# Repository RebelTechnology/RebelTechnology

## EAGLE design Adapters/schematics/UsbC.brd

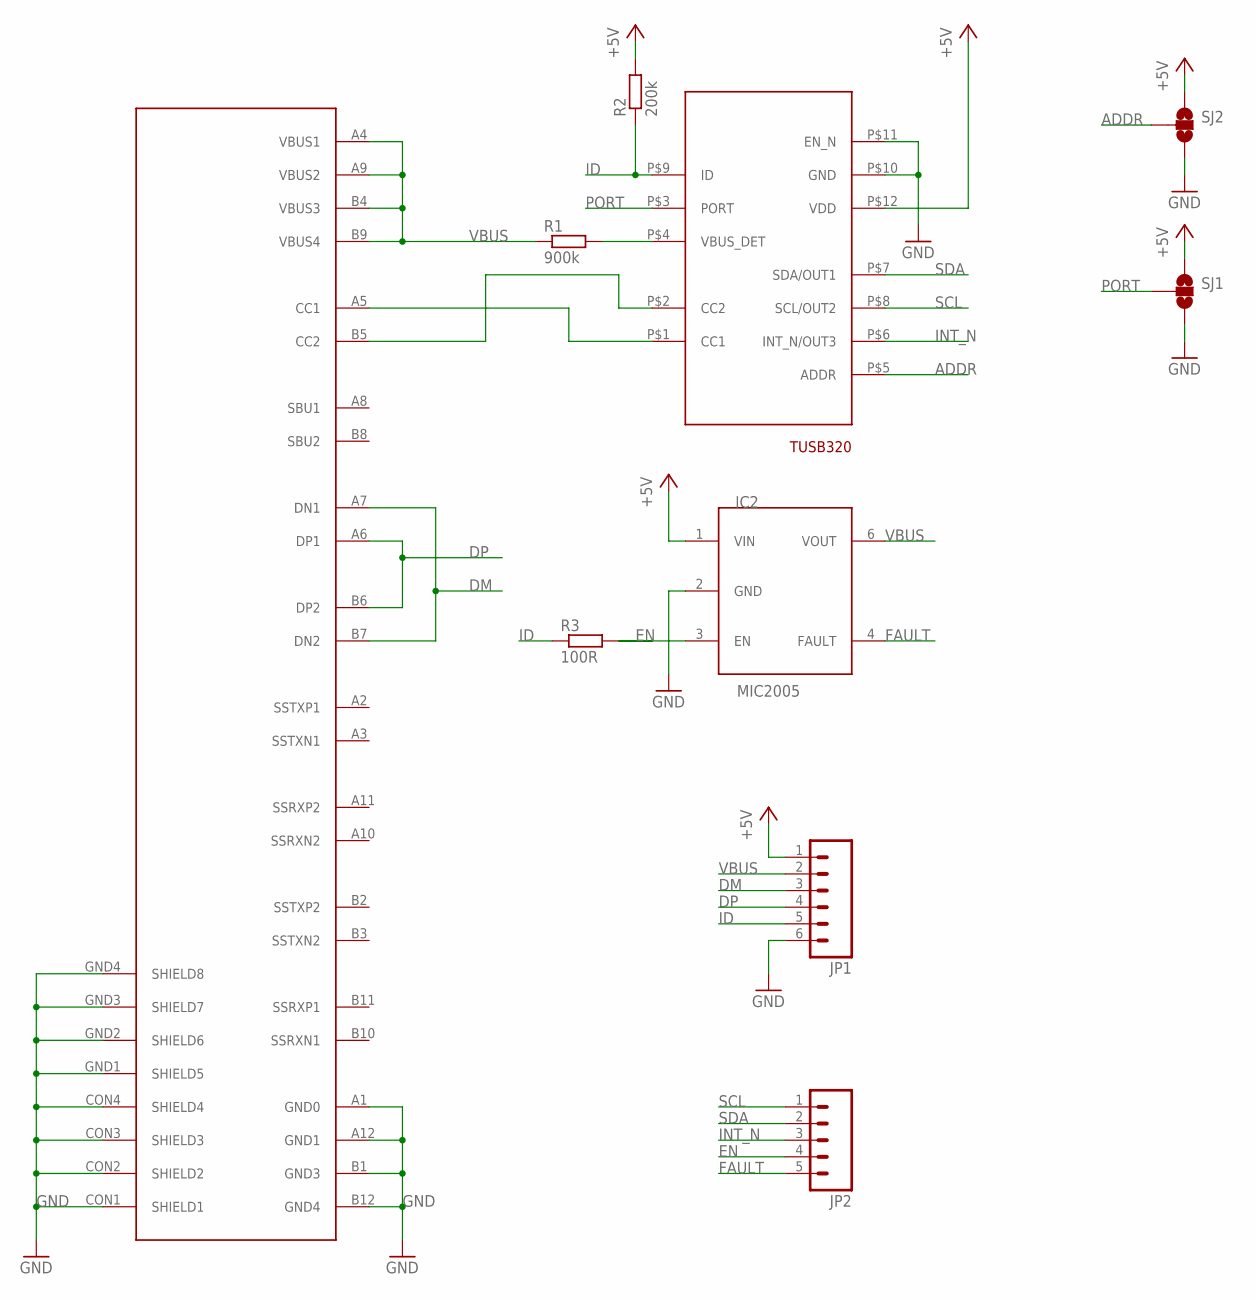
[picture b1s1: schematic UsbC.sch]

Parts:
CONN1: USB-C_WURTH_632723X00011USB-C; USB-C_WURTH_632723X00011
IC1: TUSB320XQFN; X2QFN
IC2: MIC2005; SOT23-6
JP1: M06SIP; 1X06
JP2: M05PTH; 1X05
R1: 900k; 0603
R2: 200k; 0603
R3: 100R; 0603
SJ1, SJ2: SOLDERJUMPER_2WAYS; SJ_3

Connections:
+5V: IC1.P$12 (VDD), IC2.1 (VIN), JP1.1, R2.2, SJ1.1, SJ2.1
ADDR: IC1.P$5 (ADDR), SJ2.2
CC1: CONN1.A5 (CC1), IC1.P$1 (CC1)
CC2: CONN1.B5 (CC2), IC1.P$2 (CC2)
DM: CONN1.A7 (DN1), CONN1.B7 (DN2), JP1.3
DP: CONN1.A6 (DP1), CONN1.B6 (DP2), JP1.4
EN: IC2.3 (EN), JP2.4, R3.2
FAULT: IC2.4 (FAULT), JP2.5
GND: CONN1.A1 (GND0), CONN1.A12 (GND1), CONN1.B1 (GND3), CONN1.B12 (GND4), CONN1.CON1 (SHIELD1), CONN1.CON2 (SHIELD2), CONN1.CON3 (SHIELD3), CONN1.CON4 (SHIELD4), CONN1.GND1 (SHIELD5), CONN1.GND2 (SHIELD6), CONN1.GND3 (SHIELD7), CONN1.GND4 (SHIELD8), IC1.P$10 (GND), IC1.P$11 (EN_N), IC2.2 (GND), JP1.6, SJ1.3, SJ2.3
ID: IC1.P$9 (ID), JP1.5, R2.1, R3.1
INT_N: IC1.P$6 (INT_N/OUT3), JP2.3
unnamed: IC1.P$4 (VBUS_DET), R1.2
PORT: IC1.P$3 (PORT), SJ1.2
SCL: IC1.P$8 (SCL/OUT2), JP2.1
SDA: IC1.P$7 (SDA/OUT1), JP2.2
VBUS: CONN1.A4 (VBUS1), CONN1.A9 (VBUS2), CONN1.B4 (VBUS3), CONN1.B9 (VBUS4), IC2.6 (VOUT), JP1.2, R1.1

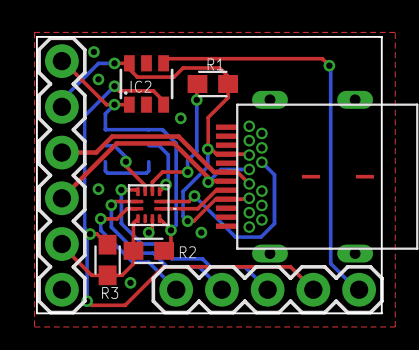
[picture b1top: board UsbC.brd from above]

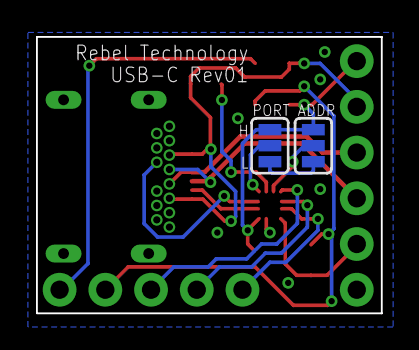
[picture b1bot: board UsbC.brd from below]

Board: 2 copper layers, 19.2 x 15.4 mm, 10 parts (2 on the bottom side), 16 nets.

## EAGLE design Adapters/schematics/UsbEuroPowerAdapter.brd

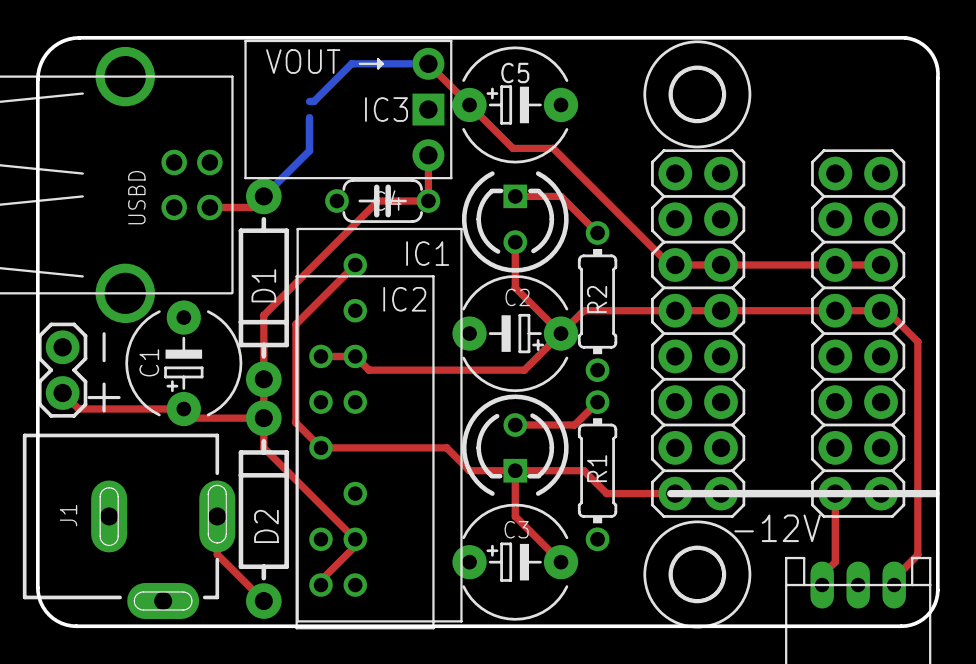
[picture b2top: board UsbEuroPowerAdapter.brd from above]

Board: 2 copper layers, 50.0 x 32.7 mm, 23 parts (1 on the bottom side), 9 nets.

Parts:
C1, C2, C3, C5: 47u; E5-6
C4: 100n; C050-024X044
D1: 1N5817; DIODE-1N4001
D2: 1N4001; DIODE-1N4001
EXT: CON-JST_PH_3W
IC1: TEC-2SIP; TEC-2
IC2: TBA-2SIP; TBA-2
IC3: REG_S9V11F5
J1: POWER_JACK; DC_JACK_SLOT
JP1: 1X02
LED1, LED2: LED3MM
R1, R2: 2k; 0204/7
U$1, U$3: 2,8
U$2, U$6: M08X2; 2X8
USBD: USB-B-H
VBUS_5V: SOLDERJUMPERNO; SJ_2S-NO

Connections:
+5V: C5.+, IC3.VOUT, U$2.11, U$2.12, U$6.11, U$6.12, VBUS_5V.2
+9V: C1.+, C4.1, D1.C, D2.C, IC1.P2, IC2.P1, IC3.VIN, JP1.2
+12V: C2.+, EXT.P3, IC1.P6, IC2.P6, LED2.A, U$2.9, U$2.10, U$6.9, U$6.10
-12V: C3.-, EXT.P1, IC1.P8, IC2.P4, LED1.K, U$2.1, U$2.2, U$6.1, U$6.2
EXT_USB_D_VBUS: D1.A, USBD.VBUS, VBUS_5V.1
GND: C1.-, C2.-, C3.+, C4.2, C5.-, EXT.P2, IC1.P1, IC1.P7, IC2.P2, IC2.P5, IC3.GND, J1.GND, J1.GNDBREAK, JP1.1, R1.1, R2.1, U$2.3, U$2.4, U$2.5, U$2.6, U$2.7, U$2.8, U$6.3, U$6.4, U$6.5, U$6.6, U$6.7, U$6.8, USBD.GND
unnamed: LED2.K, R2.2
unnamed: LED1.A, R1.2
unnamed: D2.A, J1.PWR

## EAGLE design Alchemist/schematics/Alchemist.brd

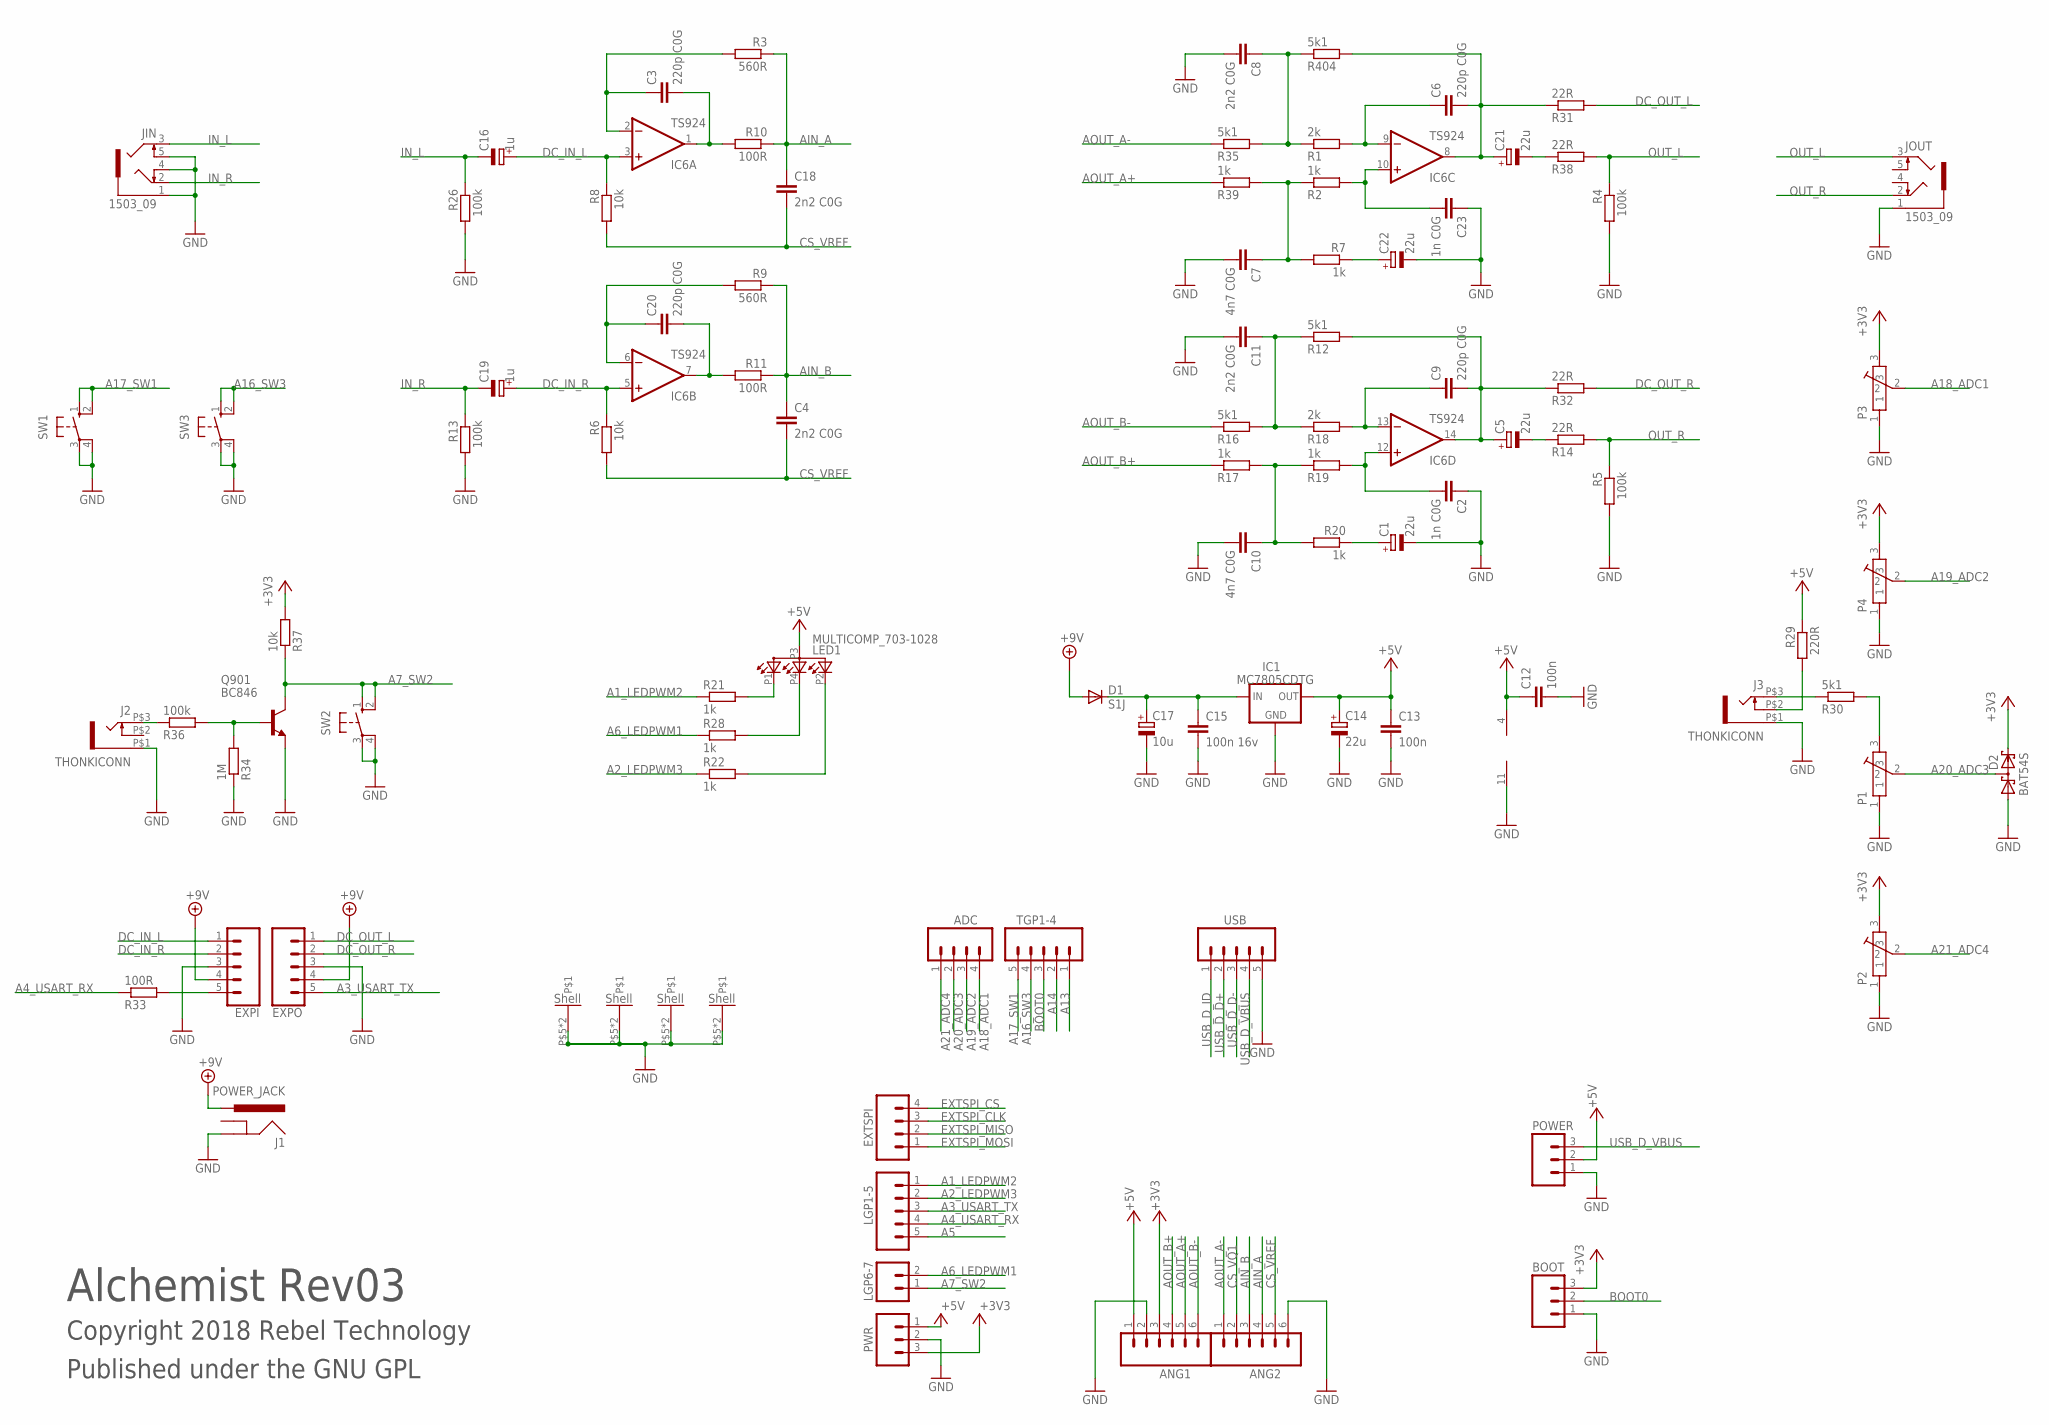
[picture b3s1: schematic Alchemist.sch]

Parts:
ADC: M04PTH; 1X04
ANG1, ANG2: M06SIP; 1X06
BOOT: M03PTH; 1X03
C1, C5, C14, C21, C22: 22u; CPOL-5
C2, C23: 1n C0G; C0603
C3, C6, C9, C20: 220p C0G; C0603
C4, C8, C11, C18: 2n2 C0G; C0603
C7, C10: 4n7 C0G; C0603
C12, C13: 100n; C0603
C15: 100n 16v; C0603
C16, C19: 1u; 153CLV-0405
C17: 10u; 153CLV-0405
D1: S1J; SMA-DIODE
D2: BAT54S; SOT23
EXPI: CONN_05JST-VERT; JST-5-PTH-VERT
EXPO: CONN_05JST-VERT; JST-5-PTH-VERT
EXTSPI: M04PTH; 1X04
IC1: MC7805CDTG; DPACK
IC6: TS924; SO14
J1: POWER_JACK; DC_JACK_SLOT
J2, J3: THONKICONN
JIN: 1503_09
JOUT: 1503_09
LED1: MULTICOMP_703-1028; RGB-LED-703-1028
LGP1-5: M05PTH; 1X05
LGP6-7: M02PTH; 1X02
P1, P2, P3, P4: POT-ALPS-RK09L1140
POWER: M03PTH; 1X03
PWR: M03PTH; 1X03
Q901: BC846; SOT23
R1, R18: 2k; 0603
R2, R7, R17, R19, R20, R21, R22, R28, R39: 1k; 0603
R3, R9: 560R; 0603
R4, R5, R13, R26, R36: 100k; 0603
R6, R8, R37: 10k; 0603
R10, R11, R33: 100R; 0603
R12, R16, R30, R35, R404: 5k1; 0603
R14, R31, R32, R38: 22R; 0603
R29: 220R; 0603
R34: 1M; 0603
SW1, SW2, SW3: 10-XX; B3F-10XX
TGP1-4: M05PTH; 1X05
USB: M05PTH; 1X05

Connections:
+3V3: ANG1.3, BOOT.3, D2.2 (C2), P2.3, P3.3, P4.3, PWR.3, R37.2
+5V: ANG1.1, C12.1, C13.1, C14.+, IC1.3 (OUT), IC6.4 (V+), LED1.P3 (A), POWER.2, PWR.1, R29.1
+9V: D1.A, EXPI.4, EXPO.4, J1.PWR
A1_LEDPWM2: LGP1-5.1, R21.1
A2_LEDPWM3: LGP1-5.2, R22.1
A3_USART_TX: EXPO.5, LGP1-5.3
A4_USART_RX: LGP1-5.4, R33.1
A5: LGP1-5.5
A6_LEDPWM1: LGP6-7.2, R28.1
A7_SW2: LGP6-7.1, Q901.3 (C), R37.1, SW2.1 (S), SW2.2 (S1)
A13: TGP1-4.1
A14: TGP1-4.2
A16_SW3: SW3.1 (S), SW3.2 (S1), TGP1-4.4
A17_SW1: SW1.1 (S), SW1.2 (S1), TGP1-4.5
A18_ADC1: ADC.4, P3.2
A19_ADC2: ADC.3, P4.2
A20_ADC3: ADC.2, D2.3 (C1A2), P1.2
A21_ADC4: ADC.1, P2.2
AIN_A: ANG2.4, C18.1, R3.1, R10.1
AIN_B: ANG2.3, C4.1, R9.1, R11.1
AOUT_A+: ANG1.5, R39.1
AOUT_A-: ANG2.1, R35.1
AOUT_B+: ANG1.4, R17.1
AOUT_B-: ANG1.6, R16.1
BOOT0: BOOT.2, TGP1-4.3
CS_VQ1: ANG2.2
CS_VREF: ANG2.5, C4.2, C18.2, R6.2, R8.2
DC_IN_L: C16.+, EXPI.1, IC6.3 (+IN), R8.1
DC_IN_R: C19.+, EXPI.2, IC6.5 (+IN), R6.1
DC_OUT_L: EXPO.1, R31.2
DC_OUT_R: EXPO.2, R32.2
EXTSPI_CLK: EXTSPI.3
EXTSPI_CS: EXTSPI.4
EXTSPI_MISO: EXTSPI.2
EXTSPI_MOSI: EXTSPI.1
GND: ANG1.2, ANG2.6, BOOT.1, C1.-, C2.1, C7.2, C8.2, C10.2, C11.2, C12.2, C13.2, C14.-, C15.2, C17.-, C22.-, C23.1, D2.1 (A1), EXPI.3, EXPO.3, IC1.4 (GND), IC6.11 (V-), J1.GND, J2.P$1 (5), J3.P$1 (5), JIN.1, JIN.4, JIN.5, JOUT.1, P1.1, P1.P$5, P1.P$6, P2.1, P2.P$5, P2.P$6, P3.1, P3.P$5, P3.P$6, P4.1, P4.P$5, P4.P$6, POWER.1, PWR.2, Q901.2 (E), R4.2, R5.2, R13.2, R26.2, R34.1, SW1.3, SW1.4 (P1), SW2.3, SW2.4 (P1), SW3.3, SW3.4 (P1), USB.5
IN_L: C16.-, JIN.3, R26.1
IN_R: C19.-, JIN.2, R13.1
unnamed: EXPI.5, R33.2
unnamed: C3.1, IC6.2 (-IN), R3.2
unnamed: C20.2, IC6.7 (OUT), R11.2
unnamed: C20.1, IC6.6 (-IN), R9.2
unnamed: C3.2, IC6.1 (OUT), R10.2
unnamed: C6.1, IC6.9 (-IN), R1.2
unnamed: C1.+, R20.1
unnamed: C21.-, R38.1
unnamed: C22.+, R7.1
unnamed: C23.2, IC6.10 (+IN), R2.2
unnamed: C5.+, C9.2, IC6.14 (OUT), R12.2, R32.1
unnamed: C5.-, R14.1
unnamed: C7.1, R2.1, R7.2, R39.2
unnamed: LED1.P1 (CRED), R21.2
unnamed: LED1.P2 (CGREEN), R22.2
unnamed: LED1.P4 (CBLUE), R28.2
unnamed: J2.P$3 (3), R36.1
unnamed: J3.P$2 (4), R29.2
unnamed: C11.1, R12.1, R16.2, R18.1
unnamed: P1.3, R30.2
unnamed: C9.1, IC6.13 (-IN), R18.2
unnamed: J3.P$3 (3), R30.1
unnamed: C15.1, C17.+, D1.C, IC1.1 (IN)
unnamed: C2.2, IC6.12 (+IN), R19.2
unnamed: C10.1, R17.2, R19.1, R20.2
unnamed: Q901.1 (B), R34.2, R36.2
unnamed: C6.2, C21.+, IC6.8 (OUT), R31.1, R404.2
unnamed: C8.1, R1.1, R35.2, R404.1
OUT_L: JOUT.3, R4.1, R38.2
OUT_R: JOUT.2, R5.1, R14.2
USB_D_D+: USB.2
USB_D_D-: USB.3
USB_D_ID: USB.1
USB_D_VBUS: POWER.3, USB.4

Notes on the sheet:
Alchemist Rev03
Copyright 2018 Rebel Technology
Published under the GNU GPL

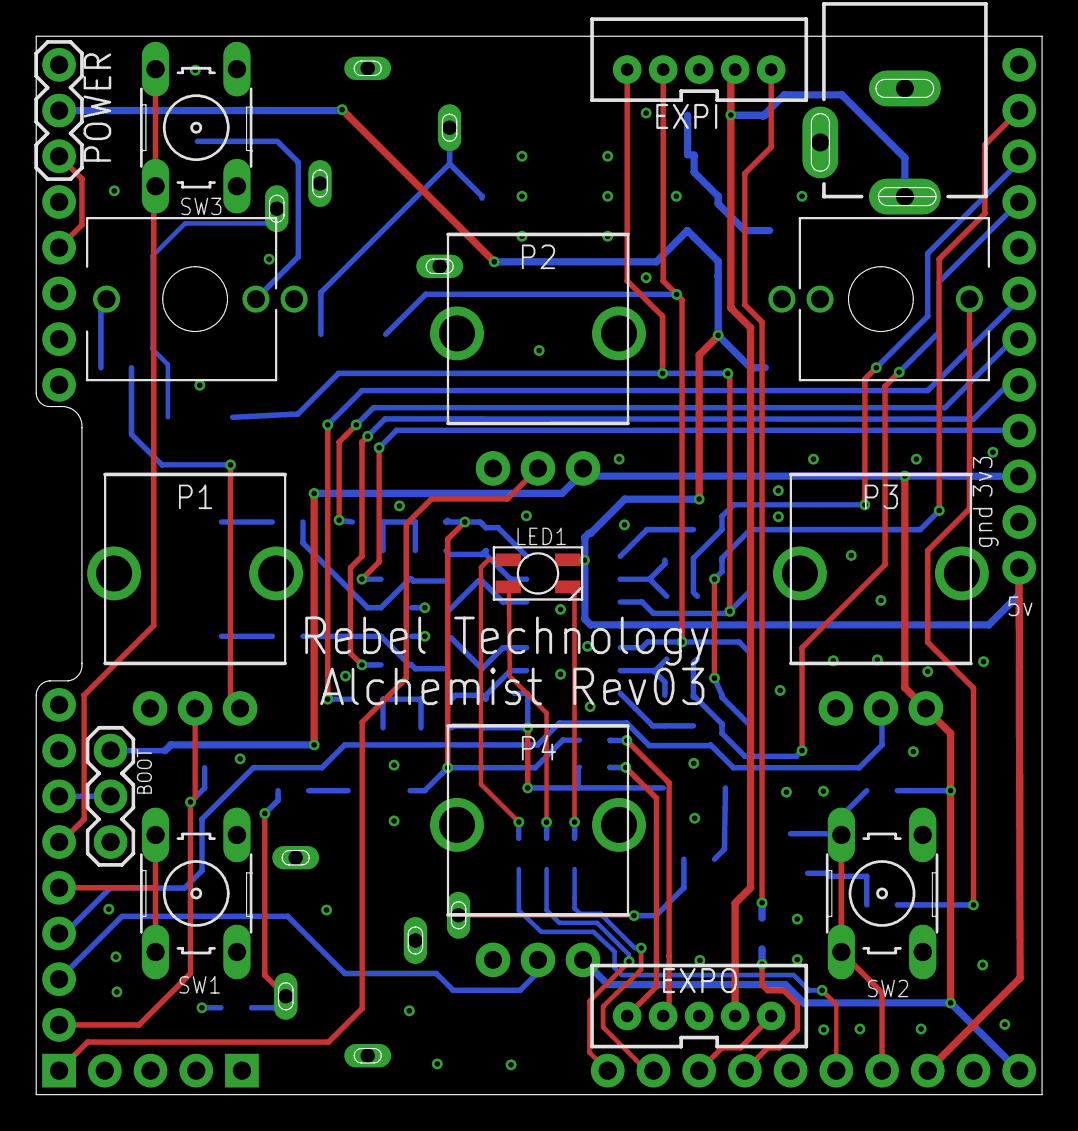
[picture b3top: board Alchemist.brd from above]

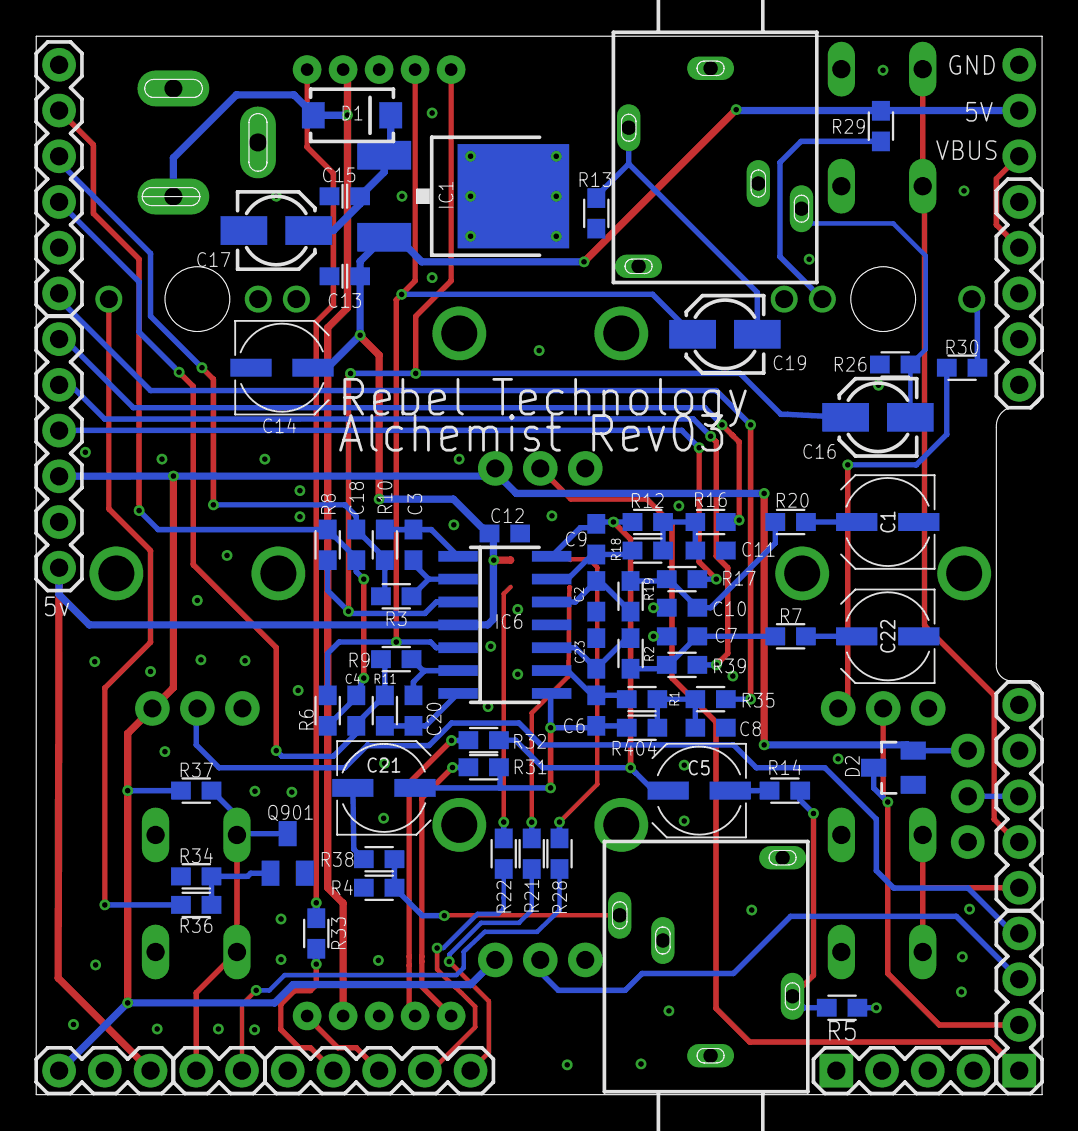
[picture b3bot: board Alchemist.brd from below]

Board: 2 copper layers, 55.9 x 58.8 mm, 89 parts (74 on the bottom side), 61 nets.

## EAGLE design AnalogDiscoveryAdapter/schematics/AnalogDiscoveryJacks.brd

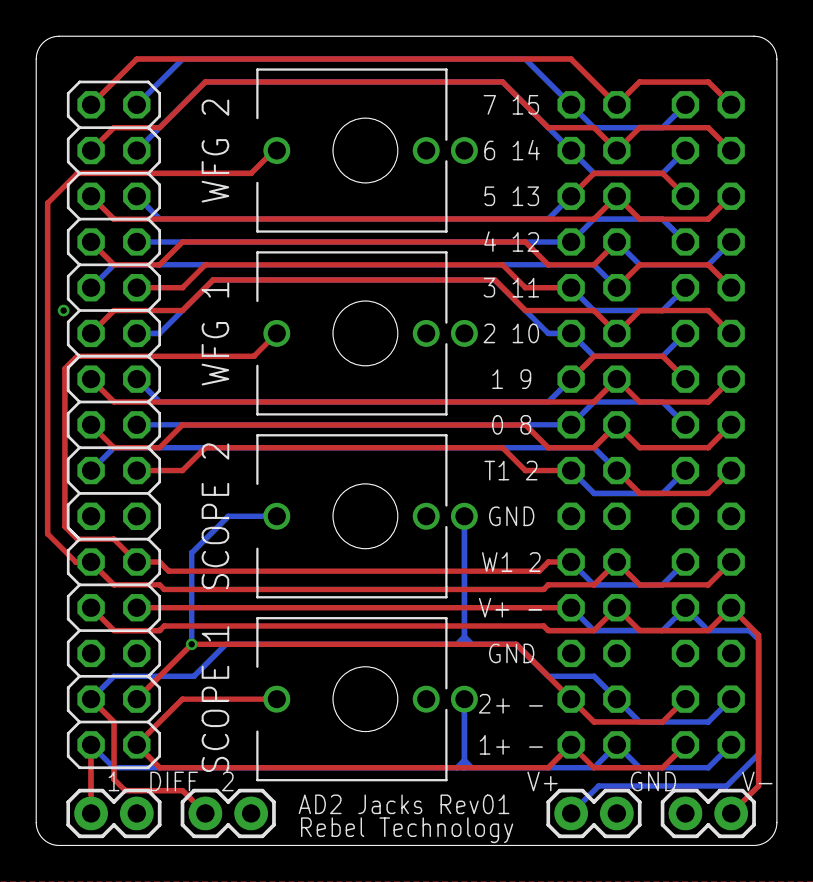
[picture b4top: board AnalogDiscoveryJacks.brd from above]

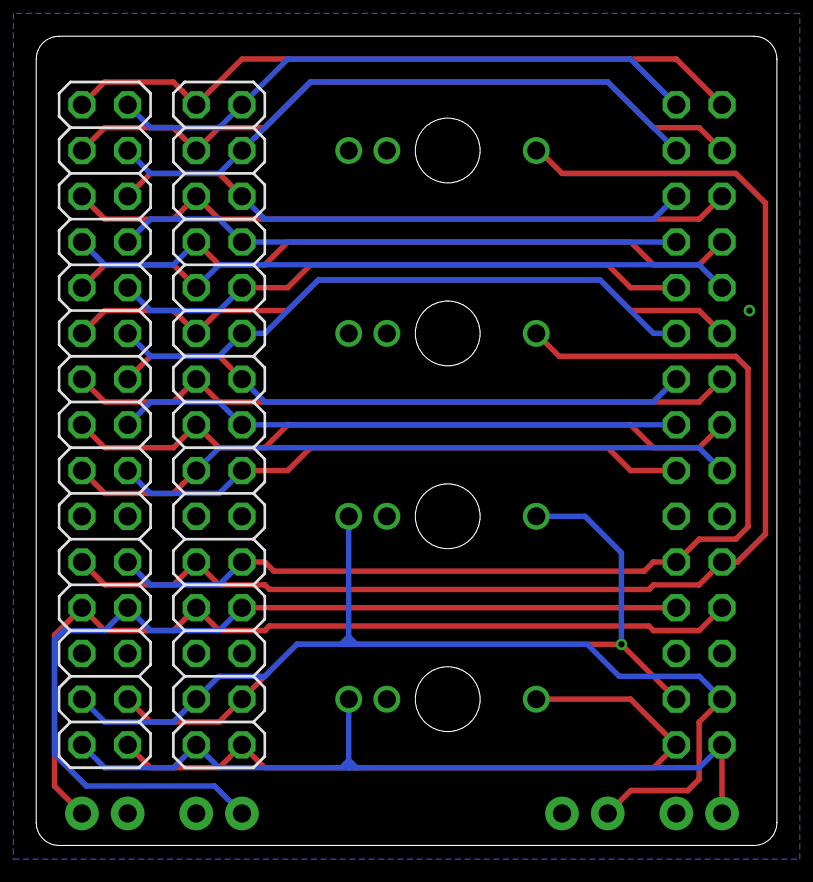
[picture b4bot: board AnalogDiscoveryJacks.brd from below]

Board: 2 copper layers, 41.1 x 45.0 mm, 11 parts (2 on the bottom side), 27 nets.

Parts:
J1, J2, J3, J4: THONKICONN
JMP1, JMP2, JMP3, JMP4: 1X02
JP1, JP2, JP3: 2X15

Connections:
D0: JP1.15, JP2.15, JP3.15
D1: JP1.17, JP2.17, JP3.17
D2: JP1.19, JP2.19, JP3.19
D3: JP1.21, JP2.21, JP3.21
D4: JP1.23, JP2.23, JP3.23
D5: JP1.25, JP2.25, JP3.25
D6: JP1.27, JP2.27, JP3.27
D7: JP1.29, JP2.29, JP3.29
D8: JP1.16, JP2.16, JP3.16
D9: JP1.18, JP2.18, JP3.18
D10: JP1.20, JP2.20, JP3.20
D11: JP1.22, JP2.22, JP3.22
D12: JP1.24, JP2.24, JP3.24
D13: JP1.26, JP2.26, JP3.26
D14: JP1.28, JP2.28, JP3.28
D15: JP1.30, JP2.30, JP3.30
GND: J3.P$1, J4.P$1, JMP1.2, JMP2.2, JMP3.2, JMP4.2, JP1.5, JP1.6, JP1.11, JP1.12, JP2.5, JP2.6, JP2.11, JP2.12, JP3.5, JP3.6, JP3.11, JP3.12
S1+: J1.P$3, JP1.1, JP2.1, JP3.1
S1-: J1.P$1, JMP1.1, JP1.2, JP2.2, JP3.2
S2+: J2.P$3, JP1.3, JP2.3, JP3.3
S2-: J2.P$1, JMP2.1, JP1.4, JP2.4, JP3.4
T1: JP1.13, JP2.13, JP3.13
T2: JP1.14, JP2.14, JP3.14
V+: JMP3.1, JP1.7, JP2.7, JP3.7
V-: JMP4.1, JP1.8, JP2.8, JP3.8
W1: J3.P$3, JP1.9, JP2.9, JP3.9
W2: J4.P$3, JP1.10, JP2.10, JP3.10

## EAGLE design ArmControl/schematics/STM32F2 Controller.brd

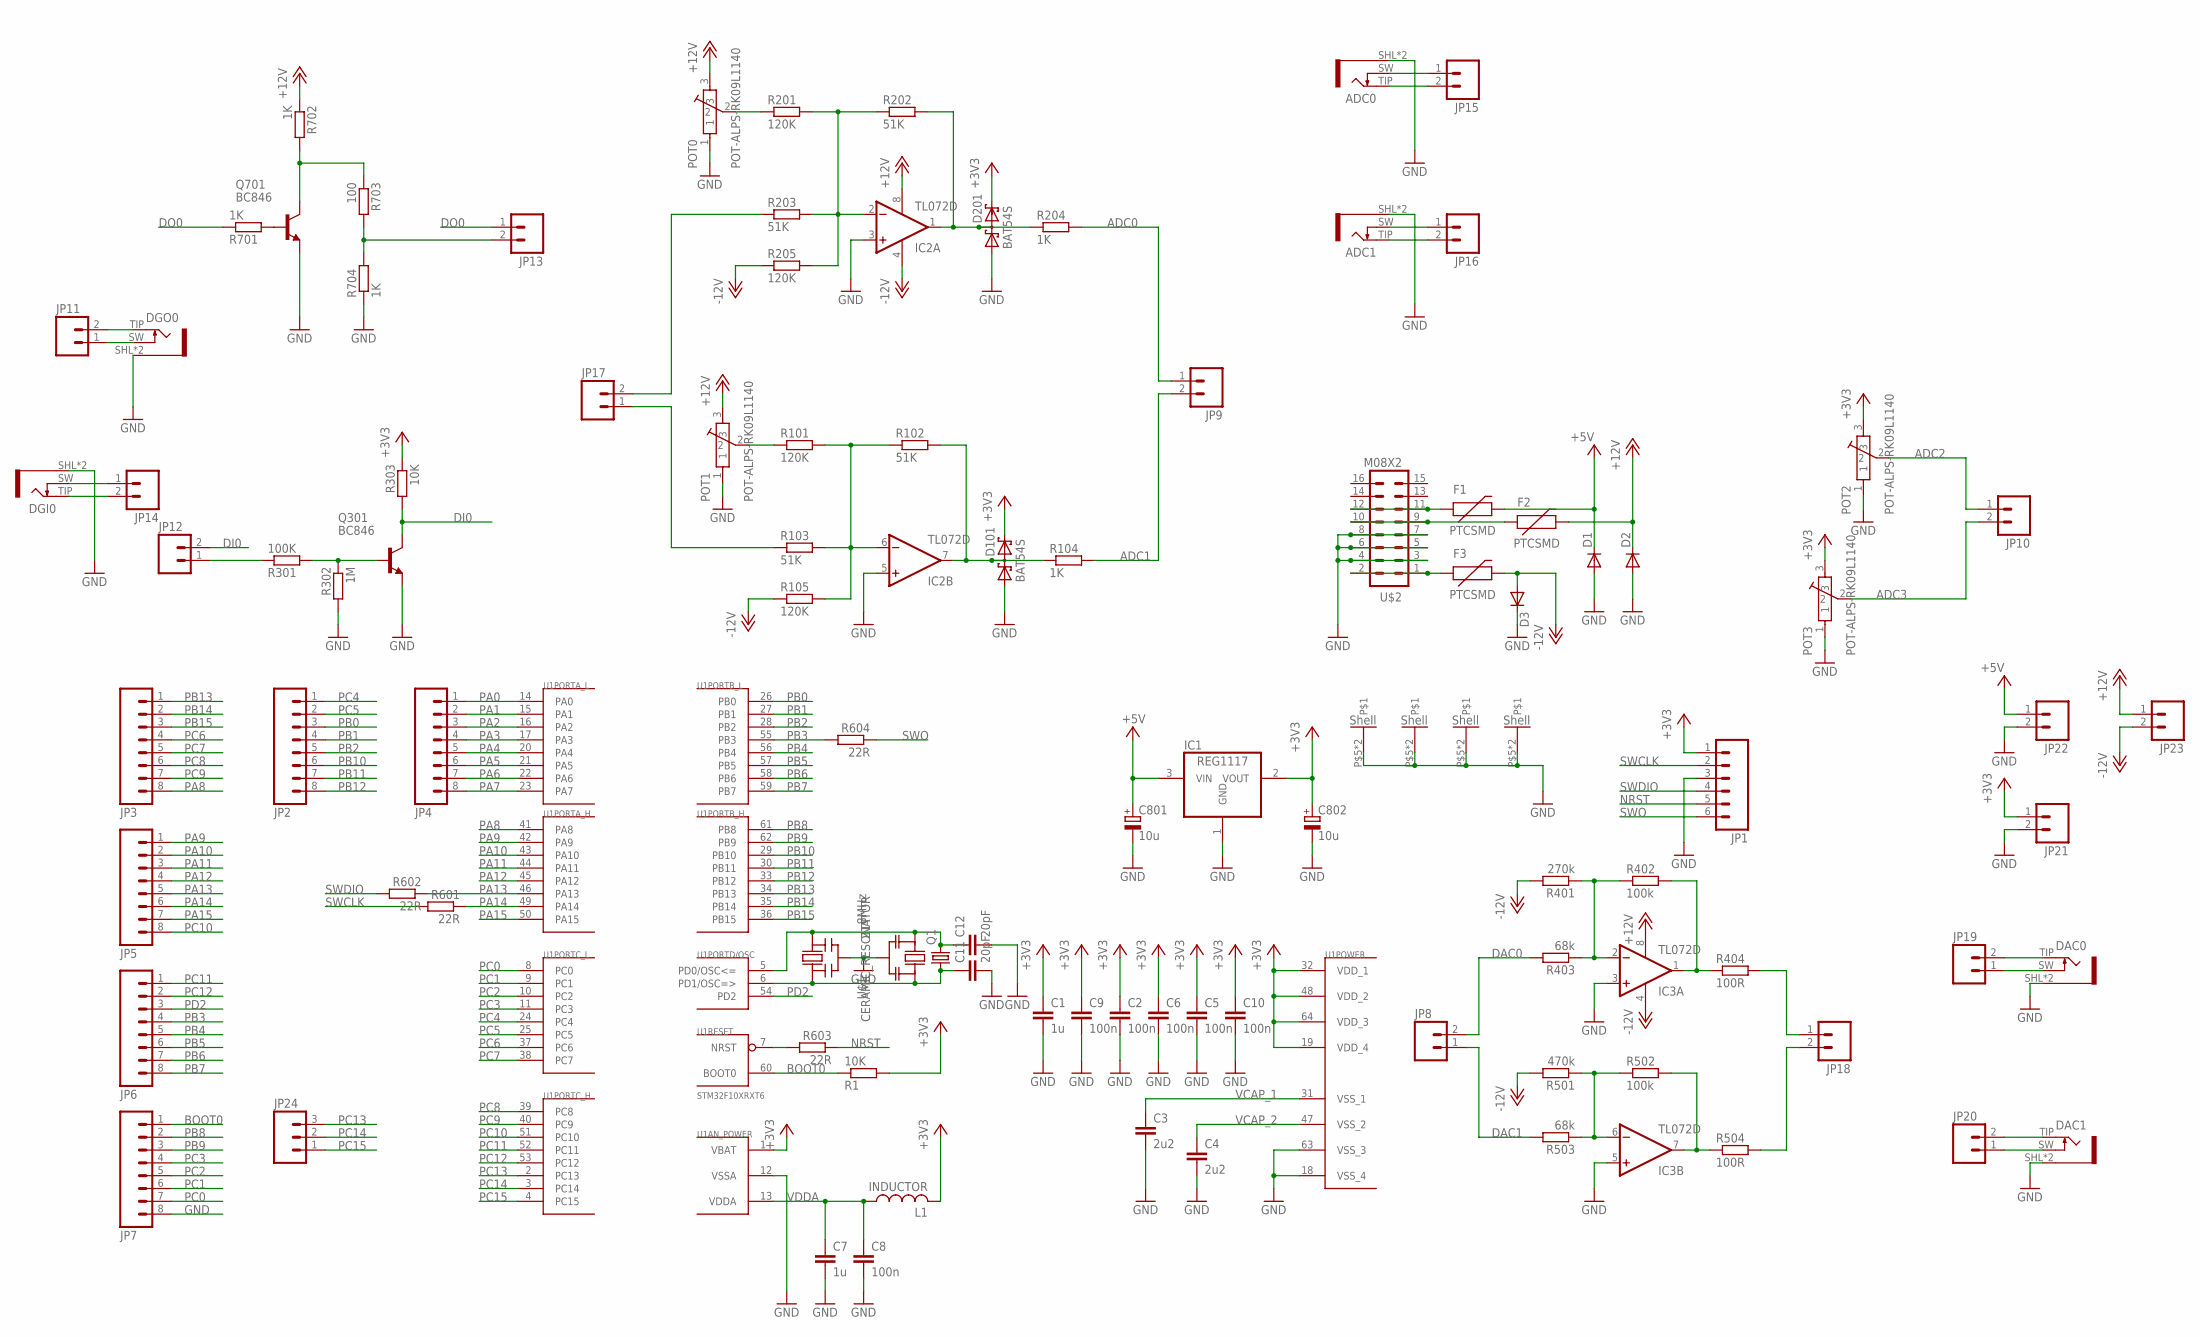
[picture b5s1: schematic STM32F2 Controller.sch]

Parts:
ADC0, ADC1: JACK-PJ-301B; PJ-301B
C1, C7: 1u; C0603
C2, C5, C6, C8, C9, C10: 100n; C0603
C3, C4: 2u2; C0603
C11, C12: 20pF; C0603
C801, C802: 10u; PANASONIC_A
D1, D2, D3: DIODESMA; SMA-DIODE
D101, D201: BAT54S; SOT23
DAC0, DAC1: JACK-PJ-301B; PJ-301B
DGI0: JACK-PJ-301B; PJ-301B
DGO0: JACK-PJ-301B; PJ-301B
F1, F2, F3: PTCSMD; PTC-1206
IC1: REG1117; SOT223
IC2, IC3: TL072D; SO08
JP1: M06SIP; 1X06
JP2, JP3, JP4, JP5, JP6, JP7: M081X08; 1X08
JP8, JP9, JP10, JP11, JP12, JP13, JP14, JP15, JP16, JP17, JP18, JP19, JP20, JP21, JP22, JP23: M02PTH; 1X02
JP24: M03PTH; 1X03
L1: INDUCTOR; 0603
POT0, POT1, POT2, POT3: POT-ALPS-RK09L1140
Q1: CRYSTALHC49UP; HC49UP
Q301, Q701: BC846; SOT23
R1, R303: 10K; R0603
R101, R105, R201, R205: 120K; R0603
R102, R103, R202, R203: 51K; R0603
R104, R204, R701, R702, R704: 1K; R0603
R301: 100K; R0603
R302: 1M; R0603
R401: 270k; R0603
R402, R502: 100k; R0603
R403, R503: 68k; R0603
R404, R504: 100R; R0603
R501: 470k; R0603
R601, R602, R603, R604: 22R; R0603
R703: 100; R0603
U1: STM32F10XRXT6; TQFP64
U$1: 8MHz; CSTCR-G
U$2: M08X2; 2X8
ZTT: CERAMIC_RESONATOR; CSTCE_G_A

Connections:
+3V3: C1.1, C2.1, C5.1, C6.1, C9.1, C10.1, C802.+, D101.2 (C2), D201.2 (C2), IC1.2 (VOUT), JP1.1, JP21.1, L1.2, POT2.3, POT3.3, R1.2, R303.1, U1.1 (VBAT), U1.19 (VDD_4), U1.32 (VDD_1), U1.48 (VDD_2), U1.64 (VDD_3)
+5V: C801.+, D1.C, F1.2, IC1.3 (VIN), JP22.1
+12V: D2.C, F2.2, IC2.8 (V+), IC3.8 (V+), JP23.1, POT0.3, POT1.3, R702.1
-12V: D3.A, F3.2, IC2.4 (V-), IC3.4 (V-), JP23.2, R105.1, R205.1, R401.2, R501.2
ADC0: JP9.1, R204.2
ADC1: JP9.2, R104.2
ADC2: JP10.1, POT2.2
ADC3: JP10.2, POT3.2
BOOT0: JP7.1, R1.1, U1.60 (BOOT0)
DAC0: JP8.2, R403.2
DAC1: JP8.1, R503.2
DI0: JP12.2, Q301.3 (C), R303.2
DO0: JP13.1, R701.1
GND: ADC0.SHL (SLEEVE), ADC0.SLV (SLEEVE), ADC1.SHL (SLEEVE), ADC1.SLV (SLEEVE), C1.2, C2.2, C3.2, C4.2, C5.2, C6.2, C7.2, C8.2, C9.2, C10.2, C11.2, C12.2, C801.-, C802.-, D1.A, D2.A, D3.C, D101.1 (A1), D201.1 (A1), DAC0.SHL (SLEEVE), DAC0.SLV (SLEEVE), DAC1.SHL (SLEEVE), DAC1.SLV (SLEEVE), DGI0.SHL (SLEEVE), DGI0.SLV (SLEEVE), DGO0.SHL (SLEEVE), DGO0.SLV (SLEEVE), IC1.1 (GND), IC2.3 (+IN), IC2.5 (+IN), IC3.3 (+IN), IC3.5 (+IN), JP1.3, JP7.8, JP21.2, JP22.2, POT0.1, POT0.P$5, POT0.P$6, POT1.1, POT1.P$5, POT1.P$6, POT2.1, POT2.P$5, POT2.P$6, POT3.1, POT3.P$5, POT3.P$6, Q301.2 (E), Q701.2 (E), R302.2, R704.1, U1.12 (VSSA), U1.18 (VSS_4), U1.63 (VSS_3), U$1.2 (GND), U$2.3, U$2.4, U$2.5, U$2.6, U$2.7, U$2.8, ZTT.P$2 (GND)
unnamed: ADC0.SW, JP15.1
unnamed: IC2.6 (-IN), R101.2, R102.1, R103.2, R105.2
unnamed: POT1.2, R101.1
unnamed: D101.3 (C1A2), IC2.7 (OUT), R102.2, R104.1
unnamed: IC3.7 (OUT), R502.2, R504.1
unnamed: F3.1, U$2.1, U$2.2
unnamed: IC3.1 (OUT), R402.2, R404.1
unnamed: DAC0.SW, JP19.1
unnamed: DAC0.TIP, JP19.2
unnamed: DGO0.SW, JP11.1
unnamed: DGO0.TIP, JP11.2
unnamed: IC3.2 (-IN), R401.1, R402.1, R403.1
unnamed: IC2.2 (-IN), R201.2, R202.1, R203.2, R205.2
unnamed: POT0.2, R201.1
unnamed: D201.3 (C1A2), IC2.1 (OUT), R202.2, R204.1
unnamed: ADC0.TIP, JP15.2
unnamed: IC3.6 (-IN), R501.1, R502.1, R503.1
unnamed: C12.1, Q1.2, U1.5 (PD0/OSC<=), U$1.3 (OUT), ZTT.P$1 (IN)
unnamed: C11.1, Q1.1, U1.6 (PD1/OSC=>), U$1.1 (IN), ZTT.P$3 (OUT)
unnamed: JP12.1, R301.1
unnamed: DGI0.SW, JP14.1
unnamed: DGI0.TIP, JP14.2
unnamed: ADC1.SW, JP16.1
unnamed: ADC1.TIP, JP16.2
unnamed: JP17.2, R203.1
unnamed: Q301.1 (B), R301.2, R302.1
unnamed: JP17.1, R103.1
unnamed: DAC1.SW, JP20.1
unnamed: DAC1.TIP, JP20.2
unnamed: JP18.1, R404.2
unnamed: JP18.2, R504.2
unnamed: Q701.1 (B), R701.2
unnamed: JP13.2, R703.2, R704.2
unnamed: Q701.3 (C), R702.2, R703.1
unnamed: F1.1, U$2.11, U$2.12
unnamed: F2.1, U$2.9, U$2.10
NRST: JP1.5, R603.1
PA0: JP4.1, U1.14 (PA0)
PA1: JP4.2, U1.15 (PA1)
PA2: JP4.3, U1.16 (PA2)
PA3: JP4.4, U1.17 (PA3)
PA4: JP4.5, U1.20 (PA4)
PA5: JP4.6, U1.21 (PA5)
PA6: JP4.7, U1.22 (PA6)
PA7: JP4.8, U1.23 (PA7)
PA8: JP3.8, U1.41 (PA8)
PA9: JP5.1, U1.42 (PA9)
PA10: JP5.2, U1.43 (PA10)
PA11: JP5.3, U1.44 (PA11)
PA12: JP5.4, U1.45 (PA12)
PA13: JP5.5, R602.1, U1.46 (PA13)
PA14: JP5.6, R601.1, U1.49 (PA14)
PA15: JP5.7, U1.50 (PA15)
PB0: JP2.3, U1.26 (PB0)
PB1: JP2.4, U1.27 (PB1)
PB2: JP2.5, U1.28 (PB2)
PB3: JP6.4, R604.2, U1.55 (PB3)
PB4: JP6.5, U1.56 (PB4)
PB5: JP6.6, U1.57 (PB5)
PB6: JP6.7, U1.58 (PB6)
PB7: JP6.8, U1.59 (PB7)
PB8: JP7.2, U1.61 (PB8)
PB9: JP7.3, U1.62 (PB9)
PB10: JP2.6, U1.29 (PB10)
PB11: JP2.7, U1.30 (PB11)
PB12: JP2.8, U1.33 (PB12)
PB13: JP3.1, U1.34 (PB13)
PB14: JP3.2, U1.35 (PB14)
PB15: JP3.3, U1.36 (PB15)
PC0: JP7.7, U1.8 (PC0)
PC1: JP7.6, U1.9 (PC1)
PC2: JP7.5, U1.10 (PC2)
PC3: JP7.4, U1.11 (PC3)
PC4: JP2.1, U1.24 (PC4)
PC5: JP2.2, U1.25 (PC5)
PC6: JP3.4, U1.37 (PC6)
PC7: JP3.5, U1.38 (PC7)
PC8: JP3.6, U1.39 (PC8)
PC9: JP3.7, U1.40 (PC9)
PC10: JP5.8, U1.51 (PC10)
PC11: JP6.1, U1.52 (PC11)
PC12: JP6.2, U1.53 (PC12)
PC13: JP24.3, U1.2 (PC13)
PC14: JP24.2, U1.3 (PC14)
PC15: JP24.1, U1.4 (PC15)
PD2: JP6.3, U1.54 (PD2)
RST: R603.2, U1.7 (NRST)
SWCLK: JP1.2, R601.2
SWDIO: JP1.4, R602.2
SWO: JP1.6, R604.1
VCAP_1: C3.1, U1.31 (VSS_1)
VCAP_2: C4.1, U1.47 (VSS_2)
VDDA: C7.1, C8.1, L1.1, U1.13 (VDDA)

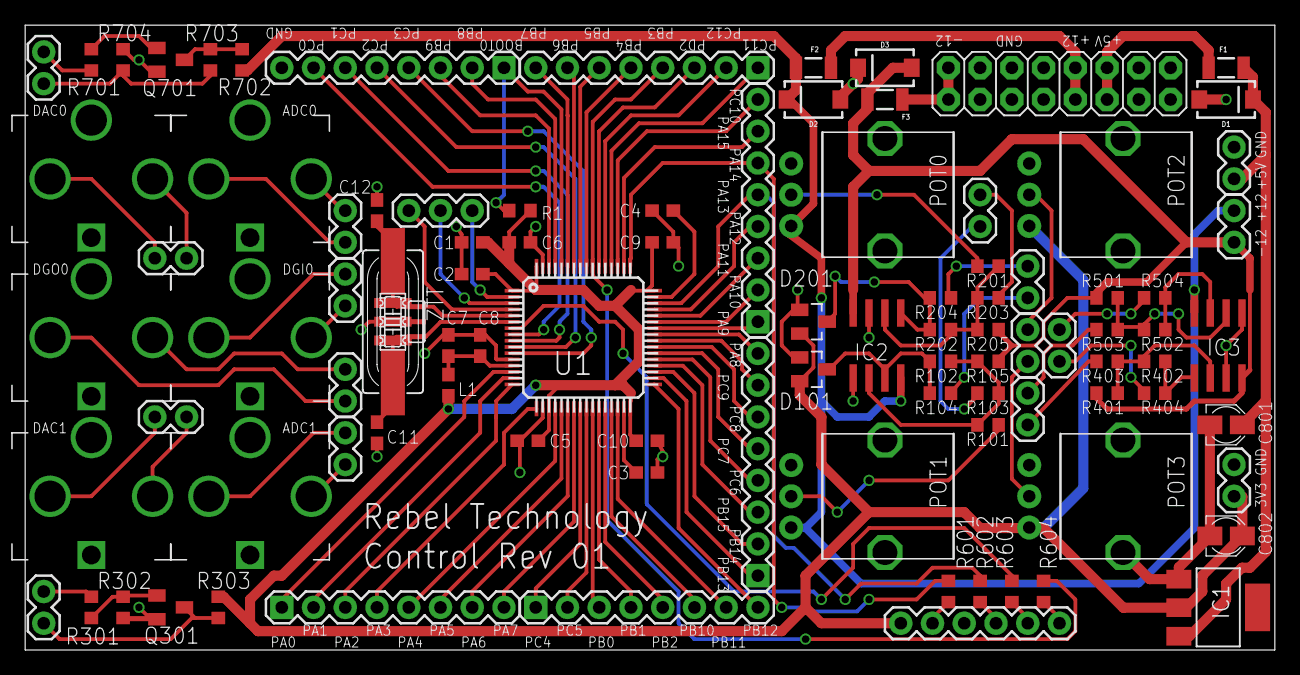
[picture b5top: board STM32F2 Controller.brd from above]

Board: 2 copper layers, 100.0 x 50.0 mm, 98 parts (0 on the bottom side), 107 nets.

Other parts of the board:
U$3: RT-LOGO-35MM-BL

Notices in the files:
parts and their libraries:
SparkFun: Licensing: CC v3.0 Share-Alike You are welcome to use this library for commercial purposes.
SparkFun-Connectors: Licensing: Creative Commons ShareAlike 4.0 International - https://creativecommons.org/licenses/by-sa/4.0
